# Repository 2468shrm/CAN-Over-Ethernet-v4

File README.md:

# CAN-Over-Ethernet-v4

A quick design that allows for using Ethernet cables to transport
both Ethernet data and CAN data.  Two pairs for Ethernet and two
for CAN.  The CAN is up and down (separated).

It is expected that one board is used at each end.

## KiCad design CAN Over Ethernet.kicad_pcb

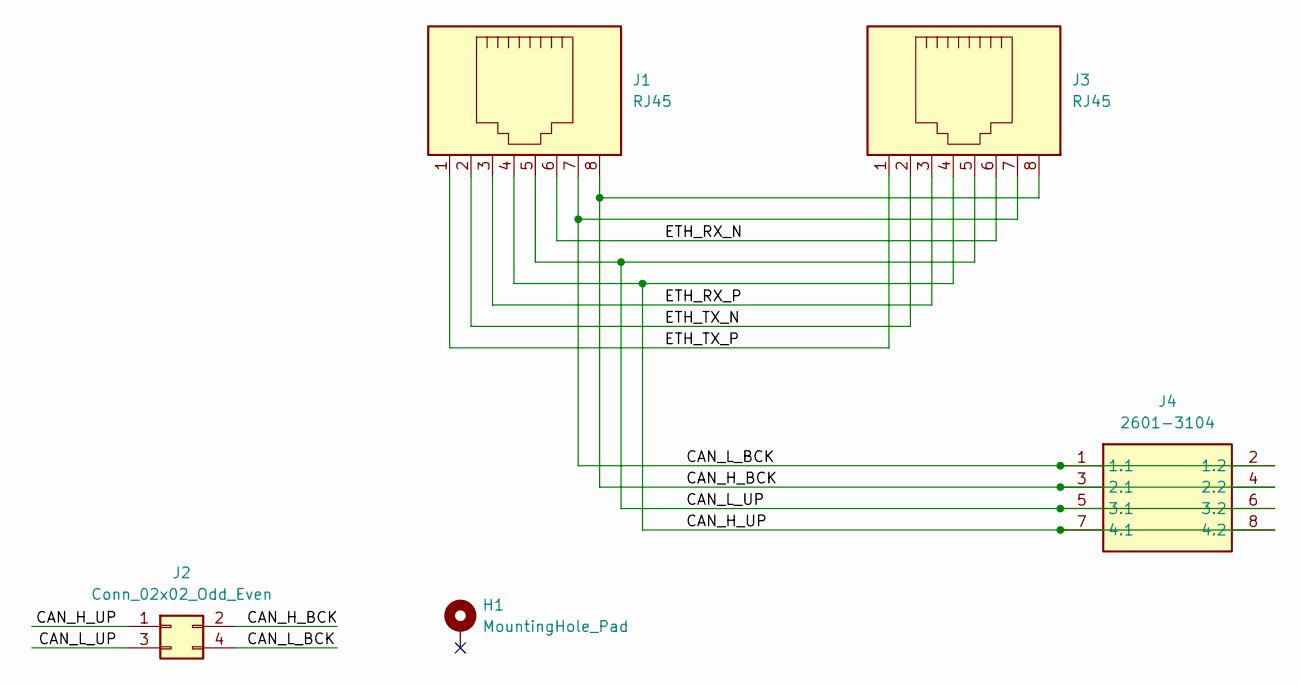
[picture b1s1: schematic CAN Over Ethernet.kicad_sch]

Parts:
H1: MountingHole_Pad; MountingHole_2.2mm_M2_DIN965_Pad
J1, J3: RJ45; RJ45_OST_PJ012-8P8CX_Vertical
J2: Conn_02x02_Odd_Even; PinHeader_2x02_P2.54mm_Vertical
J4: 2601-3104; 26013104; Manufacturer_Part_Number 2601-3104

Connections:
/CAN_H_BCK: J1.8, J2.2, J3.8, J4.3 (2.1), J4.4 (2.2)
/CAN_H_UP: J1.4, J2.1, J3.4, J4.7 (4.1), J4.8 (4.2)
/CAN_L_BCK: J1.7, J2.4, J3.7, J4.1 (1.1), J4.2 (1.2)
/CAN_L_UP: J1.5, J2.3, J3.5, J4.5 (3.1), J4.6 (3.2)
/ETH_RX_N: J1.6, J3.6
/ETH_RX_P: J1.3, J3.3
/ETH_TX_N: J1.2, J3.2
/ETH_TX_P: J1.1, J3.1

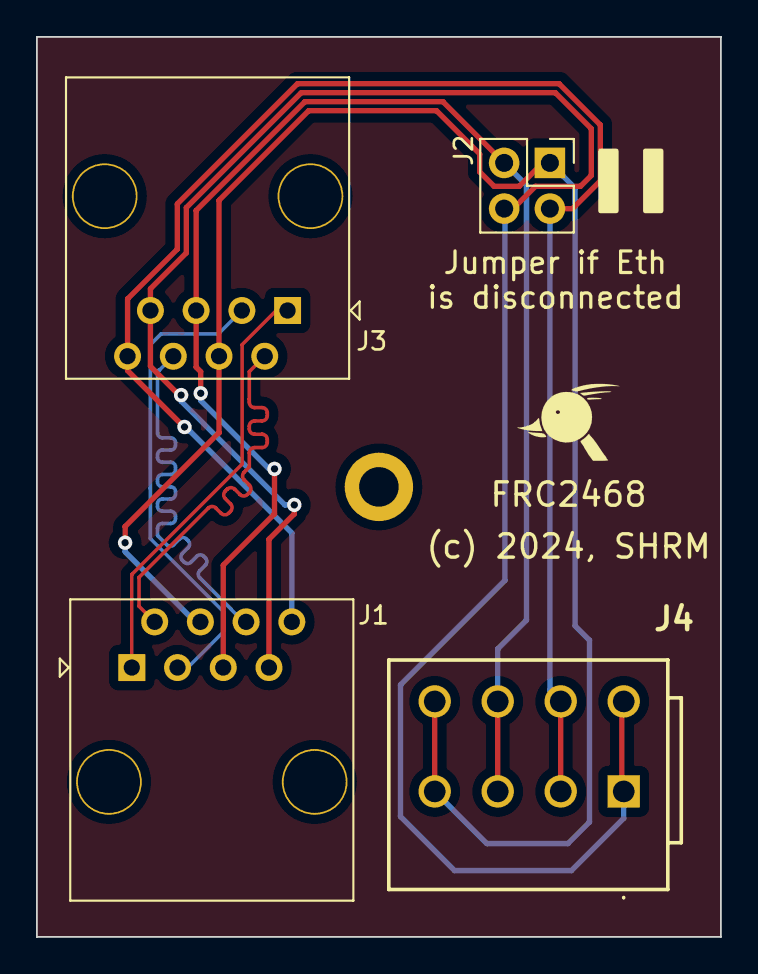
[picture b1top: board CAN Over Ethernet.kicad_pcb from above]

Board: 2 copper layers, 38.0 x 50.0 mm, 5 parts (0 on the bottom side), 8 nets.

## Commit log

2025-01-04 KiCAD files (initial)
2025-01-04 Gerber files (as sent to JLCPCB)

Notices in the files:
CAN Over Ethernet.kicad_pcb:
(c) 2024, SHRM
